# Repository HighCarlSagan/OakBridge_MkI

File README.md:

# OakBridge MkI

**A tactile PC dashboard — ESP32-S3, mechanical keys, IPS display, and a wooden enclosure.**

<p align="center">
  
  &nbsp;
  
</p>

---

## Why I Built This

I spend a lot of my day staring at terminals and dashboards. I wanted a small, tactile thing on the desk that could show me what my PC was doing without me having to alt-tab to find out — CPU temp during a long compile, what's playing on Spotify, calendar at a glance — and let me poke at it with real keys instead of yet another window.

The other half of the motivation is the stretch. OakBridge is the first project where I deliberately scoped a hardware → firmware → host-software stack end-to-end, all on parts I hadn't used in anger before: ESP32-S3, LVGL on a real display, FRAM for state, and a Python companion talking over MQTT. The point is to do the whole loop once, badly, and have a tangible thing on the desk afterwards.

The name is a nod to **oak wood** (the planned enclosure) and a small shout-out to **Oak Ridge National Laboratory**.

---

## Initial Requirements

The table below tracks the design intent against what will ship on **v1.1** (the DRC-fixed respin currently in fab, expected back end of May 2026). The first soldered board — **v1.0** — never powered up; see [Lessons Learned](#lessons-learned-the-0mm-via-incident) for the story. Until v1.1 lands, all power-up-dependent outcomes are honestly marked **TBD**.

| # | Requirement | Target | Outcome (v1.1) |
|---|---|---|---|
| 1 | MCU with WiFi + BLE + USB + enough headroom for LVGL | ESP32-S3 class | ✅ ESP32-S3-WROOM-1-N16R8 (16 MB flash, 8 MB PSRAM) |
| 2 | Display | ≥3" IPS, ≥320×240, SPI | ✅ Waveshare 3.5" IPS 320×480 (touch fanned out but unused in MkI) |
| 3 | Tactile input | Real mechanical keys with backlighting | ✅ 5× Cherry MX2A-E1NA + per-key backlight LEDs |
| 4 | Analog input | Rotary encoder with push | ✅ CUI ACZ11 (12 PPR, integrated switch) |
| 5 | Non-volatile state across reboots | FRAM, ≥1 Mbit | ✅ MB85RS4MTYPN (4 Mbit SPI FRAM) |
| 6 | Local storage for assets / logs | MicroSD socket | ✅ Hirose DM3BT push-push socket |
| 7 | Single-cable host connection | USB-C, power + serial | ✅ USB-C 2.0 + CDC-ACM virtual COM |
| 8 | Front-end protection | ESD + reverse-polarity + EMI filtering + fuse | ✅ USBLC6-2SC6 + SS14 + BLM18PG600 + 1.5A fuse |
| 9 | Power | USB 5V in, single 3.3V rail | ✅ TLV1117LV33 LDO (1A capacity, ~400 mA budget) |
| 10 | Board size | Comfortably hand-held footprint | ✅ 92 × 70 mm, 2-layer FR-4 |
| 11 | Manufacturability | Common SMD, hand-solderable | ✅ 0603 passives, QFN regulator, through-hole switches |
| 12 | Power-on bring-up | All rails verified | ⏳ TBD (waiting on v1.1) |
| 13 | Display, switches, encoder, FRAM verified | Hardware sign-off | ⏳ TBD |
| 14 | Firmware: LVGL, MQTT, OTA, mDNS | End-to-end on real board | ⏳ TBD |
| 15 | Wooden enclosure | Oak / walnut, parametric CAD | 🔄 In progress, on backburner |

---

## Specifications

| | |
|---|---|
| **MCU** | Espressif ESP32-S3-WROOM-1-N16R8 (Xtensa LX7 dual-core, 16 MB flash, 8 MB PSRAM) |
| **Display** | Waveshare 3.5" IPS, 320 × 480, SPI (touch fanned out, not wired up in firmware) |
| **Keys** | 5 × Cherry MX2A-E1NA, per-key blue backlight (Cree JE2835) |
| **Encoder** | CUI ACZ11BR1E-15KQA1-12C, 12 PPR with push |
| **NV storage** | MB85RS4MTYPN — 4 Mbit SPI FRAM |
| **Removable storage** | Hirose DM3BT-DSF-PEJS — push-push microSD socket |
| **Host interface** | USB-C 2.0, power + CDC-ACM serial |
| **Front-end protection** | 1.5 A fuse → SS14 reverse-polarity Schottky → BLM18PG600 ferrite → USBLC6-2SC6 ESD array |
| **Regulator** | TI TLV1117LV33 — 3.3 V LDO, 1 A capacity |
| **Power budget** | ~400 mA typical (estimate; bring-up will measure) |
| **PCB** | 92 × 70 mm, 2-layer FR-4, 1.6 mm, 1 oz copper, ENIG |
| **Aux switches** | BOOT + EN (ESP32 strap-pull), one extra tactile for firmware-defined use |
| **Mounting** | 4 × M3 holes (H1, H2, H6, H7) |

---

## Architecture

```
                ┌──────────────────────────────────────────────┐
                │                  USB-C (J1)                  │
                │      5 V power + USB 2.0 (D+ / D−)           │
                └──────────────────┬───────────────────────────┘
                                   │
                          ┌────────┴───────────────┐
                          │  Protection front-end  │
                          │  Fuse → SS14 → Ferrite │
                          │     → USBLC6 ESD       │
                          └────────┬───────────────┘
                                   │ 5 V
                          ┌────────┴────────┐
                          │   TLV1117LV33   │
                          │   5 V → 3.3 V   │
                          └────────┬────────┘
                                   │ 3.3 V (1 A)
                                   │
        ┌──────────────────────────┼──────────────────────────┐
        │                          │                          │
        ▼                          ▼                          ▼
┌────────────────┐       ┌─────────────────────┐    ┌───────────────────┐
│ ESP32-S3 N16R8 │       │  Waveshare 3.5" IPS │    │  MB85RS4MTYPN     │
│  WiFi + BLE    │◀─────▶│   320×480, SPI      │    │  4 Mbit SPI FRAM  │
│  USB-OTG       │       │   JST-GH 11-pin (J4)│    │   (state, config) │
└───┬────────┬───┘       └─────────────────────┘    └───────────────────┘
    │        │
    │        │            ┌──────────────────────┐
    │        ├──────────▶ │  microSD (DM3BT, J2) │
    │        │            │  logs, assets        │
    │        │            └──────────────────────┘
    │        │
    │        │            ┌──────────────────────┐
    │        └──────────▶ │  5 × Cherry MX2A     │
    │                     │  + 5 × backlight LEDs│
    │                     │  + CUI ACZ11 encoder │
    │                     │  + BOOT / EN / aux   │
    │                     └──────────────────────┘
    │
    ▼   (over WiFi)
┌──────────────────────────────┐
│  PC companion (Python)       │
│  CPU / GPU / RAM / media     │
│  → MQTT broker → OakBridge   │
└──────────────────────────────┘
```

---

## Why X over Y

A handful of decisions on this board that had real alternatives. Capturing them here so future-me remembers the trade.

**ESP32-S3 over ESP32 / RP2040.** The S3 has native USB (no CH340), enough SRAM + PSRAM to make LVGL pleasant, hardware vector ops, and WiFi + BLE on-chip. RP2040 would have been cheaper and easier to program but every wireless feature would have become a bolt-on. ESP32 (original) lacks native USB and is starting to feel its age for new designs.

**FRAM over EEPROM or flash-only.** State on this board (last screen, brightness, key bindings, MQTT credentials) gets written often enough that flash endurance is a real concern, and EEPROM is too small / too slow for anything beyond a few config bytes. FRAM is essentially RAM-fast, byte-writable, and rated for 10¹³ writes. Worth the few extra dollars.

**MicroSD + FRAM, not just FRAM.** FRAM holds *state*; SD holds *content* (UI assets, fonts, logs, image slideshow). Different access patterns, different lifetimes, different sizes. Keeping them separate keeps the firmware honest about what's small-and-precious vs. large-and-replaceable.

**TLV1117LV33 LDO over a buck.** Total budget is ~400 mA at 3.3 V from a 5 V source. Worst-case dissipation is (5 − 3.3) × 0.4 ≈ 0.7 W — comfortable for a SOT-223 with a copper pour. A buck would have been ~10–15% more efficient at the cost of switching noise on the analog encoder input, a bigger BOM, and an inductor. Not worth it at this current.

**2-layer board, not 4-layer.** Cheap to fab and the signal count is low enough to route on two layers without pain. The trade I made — and paid for — was that USB differential routing on a 2-layer stackup is fussier than I respected. See [Lessons Learned](#lessons-learned-the-0mm-via-incident). MkII may go 4-layer just for the routing comfort, not because anything on this board needs it electrically.

**Cherry MX2A over original MX.** The MX2A generation has smoother factory lubing and a quieter sound profile, and the footprint is drop-in compatible with classic MX. Same keycap ecosystem, slightly nicer feel.

**Touch fanned out but unused.** The Waveshare 3.5" comes with capacitive touch on the same FPC. I fanned the touch lines out to the connector but didn't wire them into firmware for MkI. Wanted to keep the firmware scope tractable; physical keys are the primary interaction. Touch becomes a v2 / MkII concern.

---

## Key Components

| Ref | Part | Function |
|---|---|---|
| U4 | ESP32-S3-WROOM-1-N16R8 | MCU + WiFi/BLE module |
| U3 | MB85RS4MTYPN-GS | 4 Mbit SPI FRAM |
| U2 | TLV1117LV33DCYR | 3.3 V / 1 A LDO |
| U1 | USBLC6-2SC6 | USB ESD protection array |
| J1 | GSB1C41110SSHR | USB Type-C 2.0 receptacle (Amphenol) |
| J2 | DM3BT-DSF-PEJS | Push-push microSD socket (Hirose) |
| J4 | BM11B-GHS-TBT | JST GH 11-pin (display FPC fanout) |
| MT1 | ACZ11BR1E-15KQA1-12C | CUI rotary encoder, 12 PPR + push |
| SW1–SW5 | Cherry MX2A-E1NA | Mechanical key switches |
| SW6 | TL1240YQ2JBLK | Auxiliary tactile (firmware-defined) |
| SW7, SW8 | SW_Push (THT) | ESP32 BOOT and EN |
| LED1–LED5 | Cree JE2835ARY-N | Per-key backlight (blue) |
| CR1 | SS14 | Schottky reverse-polarity protection |
| F1 | 1.5 A fuse (C1Q-series) | Input over-current |
| FL1 | BLM18PG600SN1D | EMI ferrite bead |
| R6, R7 | 5.1 kΩ | USB-C CC pull-downs (UFP role) |
| R30, R33–R35 | 0 Ω | Config straps (boot mode / interface selection) |

Full BOM: [`hardware/PC_Interface_Card/Exports/PC_Interface_Card.csv`](hardware/PC_Interface_Card/Exports/PC_Interface_Card.csv)
Netlist: [`hardware/PC_Interface_Card/Exports/PC_Interface_Card.net`](hardware/PC_Interface_Card/Exports/PC_Interface_Card.net)

---

## Connector Pinout

| Connector | Type | Purpose |
|---|---|---|
| J1 — USB-C | Amphenol GSB1C41110SSHR | 5 V power in + USB 2.0 data (UFP, CC pull-downs to GND via 5.1 kΩ) |
| J2 — microSD | Hirose DM3BT push-push | SPI to ESP32 (CD line wired) |
| J4 — Display | JST GH 11-pin | SPI MOSI/SCLK + DC/CS/RST + backlight enable + touch (unused) |
| MT1 — Encoder | Through-hole | A / B / SW pins (pull-ups on host side) |
| H1 / H2 / H6 / H7 | M3 mounting | Mechanical only |

Detailed pin-by-pin mapping will live in [`docs/pinout.md`](docs/pinout.md) once firmware development starts and pin assignments are locked.

---

## Firmware

**Status: not started.** Waiting for v1.1 boards to arrive before writing a single line. The plan below is the design intent, not a description of code that exists.

**Framework:** ESP-IDF v5.x
**Location:** `firmware/` (currently empty)

**Planned scope:**

- **Display:** LVGL on top of the Waveshare SPI driver, double-buffered, target 30+ FPS on simple screens.
- **Input:** software-debounced switches; quadrature decode for the encoder; long-press / multi-press detection.
- **Storage:** FRAM holds runtime config (brightness, current screen, key bindings, MQTT credentials). microSD holds fonts, icons, and any image assets.
- **Connectivity:** WiFi station mode, mDNS responder as `oakbridge.local`, MQTT client to a user-configured broker, embedded HTTP config server, OTA over WiFi.
- **PC link:** MQTT topics — `oakbridge/stats` (incoming PC metrics), `oakbridge/media` (now-playing), `oakbridge/commands` (outgoing key/encoder events). QoS 1.

Firmware build and flash instructions will land in [`docs/firmware_guide.md`](docs/firmware_guide.md) (planned).

### PC Companion

**Status: placeholder.** No code yet. The repo has a `companion/` directory reserved for it.

**Plan:** Python 3.8+ daemon that collects CPU / GPU / RAM / temperature stats via `psutil` and `pynvml`, reads media-player state via MPRIS on Linux, and publishes everything to MQTT for OakBridge to render. Linux first (my daily driver); Windows / macOS later if there's appetite.

---

## Setup & Bring-up

(Filled in after v1.1 boards arrive and bring-up completes.)

**Planned bring-up sequence:**

| Step | Action | Pass criterion |
|---|---|---|
| 1 | Power on via USB-C, no MCU loaded | 3.3 V rail measures 3.27–3.33 V, no thermal events |
| 2 | Probe ESP32 strap pins at reset | BOOT/EN behave correctly, no unexpected boot mode |
| 3 | Flash a minimal "hello UART" firmware | CDC-ACM enumerates, serial output visible |
| 4 | LED smoke test | Each of LED1–LED5 lights when driven |
| 5 | Switch + encoder smoke test | All 5 MX keys + encoder A/B/SW register |
| 6 | FRAM read/write test | Known-pattern write → power cycle → read back matches |
| 7 | microSD enumerate + read | FAT32 mount succeeds, files listable |
| 8 | Display init | Waveshare 3.5" shows colour bars |
| 9 | LVGL "hello" screen | First UI screen renders, encoder navigates |
| 10 | WiFi join + MQTT publish loop | `oakbridge/heartbeat` visible on broker |

Empty results table for backfill once boards arrive:

| Step | Result | Date | Notes |
|---|---|---|---|
| 1 | TBD | | |
| 2 | TBD | | |
| 3 | TBD | | |
| 4 | TBD | | |
| 5 | TBD | | |
| 6 | TBD | | |
| 7 | TBD | | |
| 8 | TBD | | |
| 9 | TBD | | |
| 10 | TBD | | |

---

## Hardware

**KiCad project:** [`hardware/PC_Interface_Card/`](hardware/PC_Interface_Card/) (KiCad 9.0)
**Schematic PDF:** [`hardware/docs/schematic.pdf`](hardware/docs/schematic.pdf)
**Gerbers:** [`hardware/PC_Interface_Card/Exports/Gerbers/`](hardware/PC_Interface_Card/Exports/Gerbers/) (v1.1, planned for end-of-May 2026)
**BOM:** [`hardware/PC_Interface_Card/Exports/PC_Interface_Card.csv`](hardware/PC_Interface_Card/Exports/PC_Interface_Card.csv)

### PCB Specifications

- **Size:** 92 × 70 mm
- **Layers:** 2-layer FR-4, 1.6 mm
- **Copper:** 1 oz (35 µm) outer
- **Finish:** ENIG
- **Min trace / clearance:** 0.15 mm / 0.15 mm (6 mil / 6 mil)
- **USB differential pair:** 0.35 mm width, 0.15 mm gap, target 90 Ω
- **Vias (v1.1):** 0.6 mm pad / 0.3 mm drill (signal); 0.8 mm / 0.4 mm (power)
- **Stitching:** ~50 GND vias

Design rule references:
- [`hardware/docs/pcb_design_rules.md`](hardware/docs/pcb_design_rules.md)
- [`hardware/docs/usb_routing_quick_ref.txt`](hardware/docs/usb_routing_quick_ref.txt)
- [`hardware/docs/kicad_design_rules.json`](hardware/docs/kicad_design_rules.json)

### Enclosure

A wooden enclosure (oak) is planned. CAD work is in progress and on the backburner while the v1.1 PCB respin and firmware bring-up take priority. Parametric files will land in [`enclosure/`](enclosure/) once the design is ready.

---

## Lessons Learned: the 0mm-via incident

The v1.0 board does not work. It does not even power up — I haven't tried, because the failure is structural, not electrical.

**What happened.** When I set up the PCB design rules in KiCad, I left the **via drill diameter at 0 mm** in one of the via classes. KiCad's DRC would have caught this immediately. I skipped DRC verification before exporting Gerbers, because the layout was "obviously fine" — I had reviewed it visually and the renders looked clean. The fab took the files as-is, produced the board with pads where vias should have been, and shipped it. I soldered the whole thing before realising every via on the affected net class was just a copper dot with no hole through the board.

**What I'm doing about it.**

1. **v1.1 is in fab.** Same design, drill diameters corrected, going turnkey this time so I get a populated board back. Expected end of May 2026.
2. **DRC is no longer optional.** From now on, "DRC pass" is a step in my export checklist that has to be ticked before Gerbers leave my machine. I've added a one-line note to my KiCad project template.
3. **I review fab DFM reports.** Most fabs *do* run DFM checks and flag missing drills. This one didn't, or did and I missed the email. Either way, the responsibility is on me to verify, not on them to warn.

**Why this is in the README and not buried.** The whole point of these write-ups is to be honest about how the work actually went. The board is broken because I made an avoidable mistake. Documenting it costs me nothing and saves the next person (probably future-me, on a different project) from doing the same thing. It also makes everything *else* in this README more credible.

More detail in [`docs/lessons-learned.md`](docs/lessons-learned.md).

---

## Repository Structure

```
OakBridge_MkI/
├── hardware/
│   ├── PC_Interface_Card/         # KiCad 9.0 project
│   │   ├── PC_Interface_Card.kicad_pro
│   │   ├── PC_Interface_Card.kicad_sch
│   │   ├── PC_Interface_Card.kicad_pcb
│   │   ├── Libraries/             # Custom symbols + footprints
│   │   └── Exports/
│   │       ├── Gerbers/
│   │       ├── PC_Interface_Card.csv     # BOM
│   │       ├── PC_Interface_Card.net     # Netlist
│   │       ├── PC_Interface_Card_Top.jpg
│   │       └── PC_Interface_Card_Bot.jpg
│   └── docs/
│       ├── schematic.pdf
│       ├── pcb_design_rules.md
│       ├── usb_routing_quick_ref.txt
│       └── kicad_design_rules.json
├── firmware/                      # ESP-IDF project (planned)
├── companion/                     # Python PC companion (placeholder)
├── enclosure/                     # Oak enclosure CAD (in progress)
├── docs/
│   ├── lessons-learned.md
│   ├── firmware_guide.md          # planned
│   ├── pinout.md                  # planned
│   └── images/
├── LICENSE
└── README.md
```

---

## When to Use This / When NOT to Use This

**Use this if you want to:**
- Build a tactile, mechanical-key dashboard for your own PC, on your own desk, with your own UI.
- Learn ESP32-S3, LVGL, FRAM, and MQTT together on one small board.
- Fork the design as a starting point for any "small wireless gadget with a screen and a few buttons" project.

**Don't use this if you want to:**
- A polished, validated, production-ready product. This is a personal learning project. v1.0 didn't power up. v1.1 is in fab.
- A keyboard. 5 keys is not a keyboard. If you want a macropad, the Cherry MX footprints are reusable but you'd be better off with a project actually scoped as a macropad.
- A low-latency input device for gaming. USB-CDC + MQTT has latencies that are fine for "skip track" and bad for "fire weapon".

---

## Roadmap

### v1.0 — soldered, dud (May 2026)
PCBs fabricated and hand-soldered. Discovered the 0mm-via DRC miss after assembly. Never powered up. Kept on the desk as a reminder.

### v1.1 — DRC-fixed respin (end of May 2026, in fab)
- ✅ Drill diameters corrected, DRC clean, Gerbers re-exported
- ⏳ Turnkey assembly with the fab — boards arrive populated
- ⏳ Power-on bring-up (table above)
- ⏳ Firmware v0.1 — display init, switches, encoder, FRAM read/write
- ⏳ Firmware v0.2 — WiFi + MQTT + first PC-companion round-trip
- 🔄 Enclosure CAD (oak) — in progress, no committed date

### MkII — possibilities (much later, ~2027)

Not committed. Listing what I'd consider if I redesigned from scratch:

- 4-layer stackup for cleaner USB / display routing
- Capacitive touch wired into firmware (FPC fanout already exists)
- USB-C PD negotiation for higher current headroom
- Side-mount encoder for a flatter front face
- Independent RGB backlight per key (currently single-channel blue)

---

## License

**Hardware:** [CERN Open Hardware Licence Version 2 — Permissive (CERN-OHL-P-2.0)](LICENSE)
**Firmware** (when it exists): MIT
**Documentation:** CC-BY-4.0

You're free to use, modify, fabricate, and distribute the hardware design with attribution. No reciprocity required.

---

## Related Projects

- **[PC_and_Light_Controller](https://github.com/HighCarlSagan/PC_and_Light_Controller)** — sibling desk-control project. PC_and_Light_Controller handles physical switching of mains-powered desk devices; OakBridge handles the on-desk informational layer. Different problems, same desk.
- **[Dual_Power_Supply](https://github.com/HighCarlSagan/Dual_Power_Supply)** — my benchtop linear supply. The supply that probed v1.0 and confirmed the bad news.
- **[Carls_Homelab_Public](https://github.com/HighCarlSagan/Carls_Homelab_Public)** — where the MQTT broker will eventually live.

---

## Author

**Mayank S (HighCarlSagan)** — [GitHub @HighCarlSagan](https://github.com/HighCarlSagan) · [highcarlsagan.dev](https://highcarlsagan.dev)

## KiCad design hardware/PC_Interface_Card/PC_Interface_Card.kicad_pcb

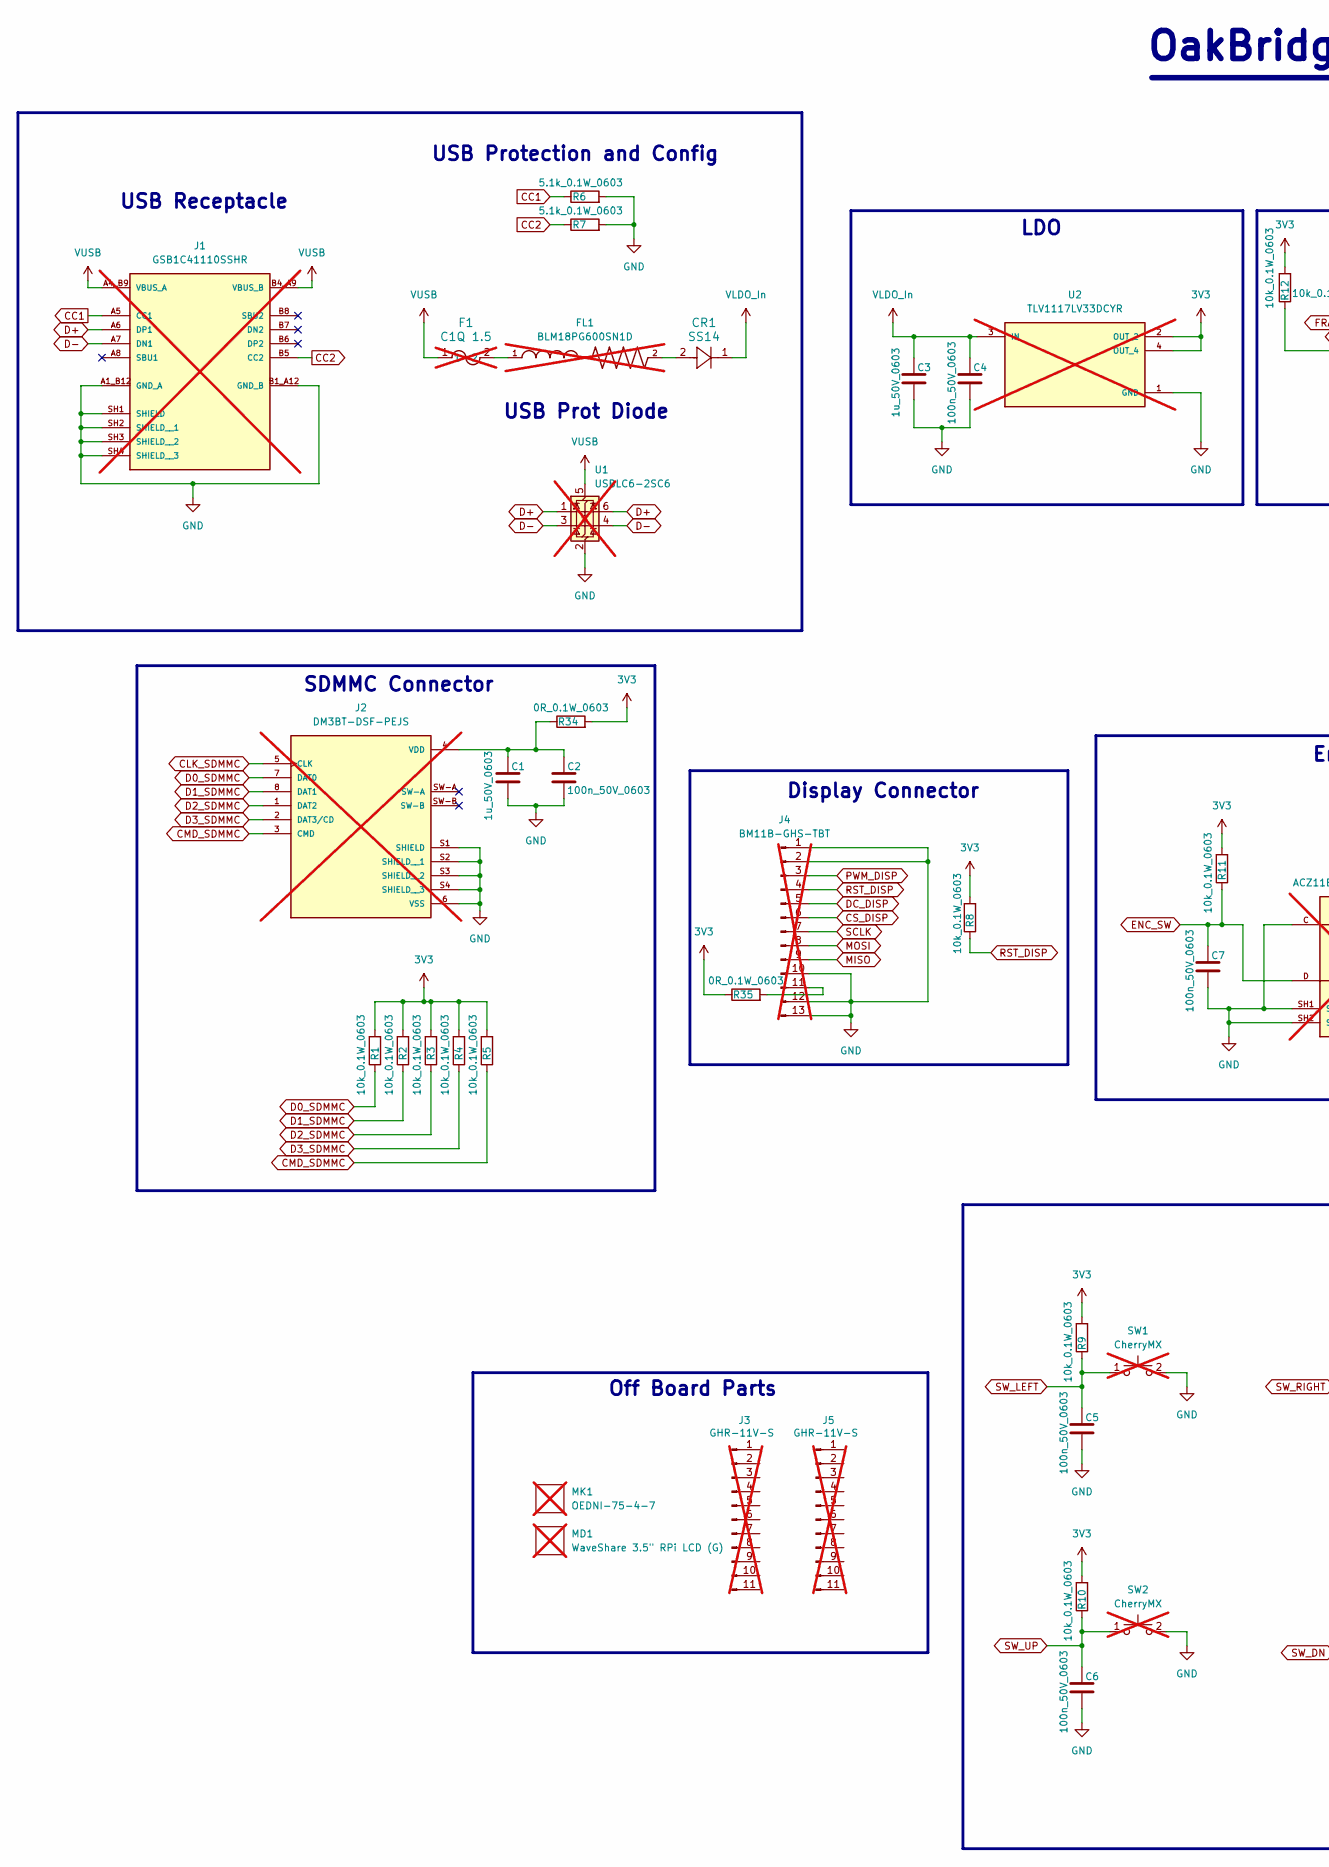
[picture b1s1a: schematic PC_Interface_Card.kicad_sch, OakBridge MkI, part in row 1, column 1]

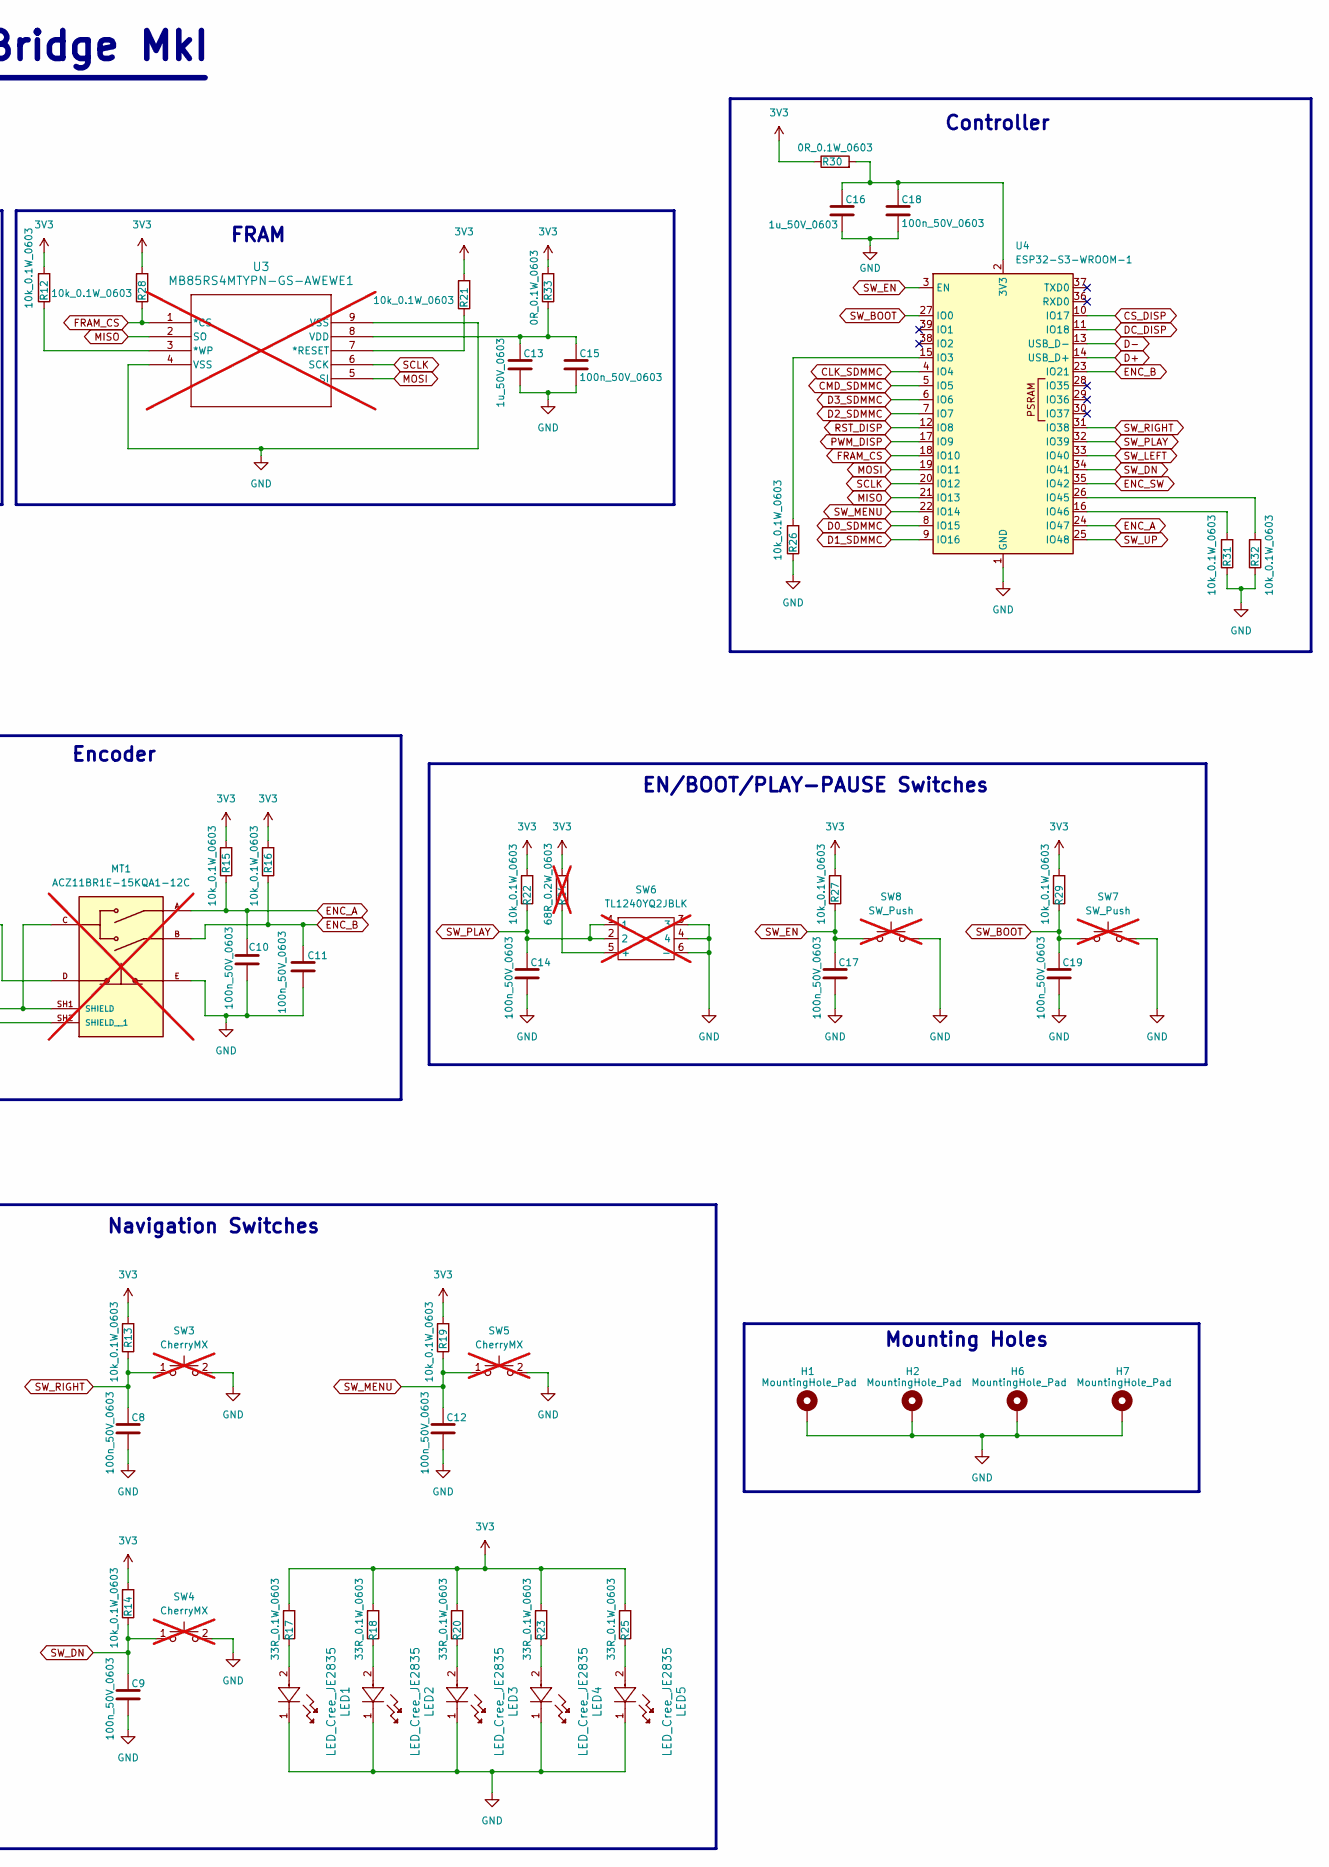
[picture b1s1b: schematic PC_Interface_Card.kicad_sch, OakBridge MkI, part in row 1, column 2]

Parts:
C1, C3, C13, C16: 1u_50V_0603; C_0603_1608Metric; Manufacturer Part Number C0603C105K4RACTU; LCSC C15849
C2, C4, C5, C6, C7, C8, C9, C10, C11, C12, C14, C15, C17, C18, C19: 100n_50V_0603; C_0603_1608Metric; Manufacturer Part Number CC0603KRX7R7BB104; LCSC C14663
CR1: SS14; D_SMA; Manufacturer Part Number SS14; LCSC C2480
F1: C1Q 1.5; C1_BEL-M; Manufacturer Part Number C1Q 1.5; not fitted
FL1: BLM18PG600SN1D; BEAD_BLM18PG_C1608X95N; Manufacturer Part Number BLM18PG600SN1D; not fitted
H1, H2, H6, H7: MountingHole_Pad; MountingHole_2.2mm_M2_Pad_Via
J1: GSB1C41110SSHR; AMPHENOL_GSB1C41110SSHR; Manufacturer Part Number GSB1C41110SSHR; not fitted
J2: DM3BT-DSF-PEJS; HRS_DM3BT-DSF-PEJS; Manufacturer Part Number DM3BT-DSF-PEJS; not fitted
J3, J5: GHR-11V-S; Manufacturer Part Number GHR-11V-S; not fitted
J4: BM11B-GHS-TBT; CONN11_BM11B-GHS-TBTLFSNN_JST; Manufacturer Part Number BM11B-GHS-TBT; not fitted
LED1, LED2, LED3, LED4, LED5: LED_Cree_JE2835; LED_JE2835_CRW-M; Manufacturer Part Number JE2835ARY-N-0002A0000-N0000001
MD1: WaveShare 3.5" RPi LCD (G); Manufacturer Part Number 30897; not fitted
MK1: OEDNI-75-4-7; Manufacturer Part Number OEDNI-75-4-7; not fitted
MT1: ACZ11BR1E-15KQA1-12C; XDCR_ACZ11BR1E-15KQA1-12C; Manufacturer Part Number ACZ11BR1E-15KQA1-12C; not fitted
R1, R2, R3, R4, R5, R8, R9, R10, R11, R12, R13, R14, R15, R16, R19, R21, R22, R26, R27, R28, R29, R31, R32: 10k_0.1W_0603; R_0603_1608Metric; Manufacturer Part Number ERJ-PB3B1002V; LCSC C25804
R6, R7: 5.1k_0.1W_0603; R_0603_1608Metric; Manufacturer Part Number ERJ-PB3B5101V; LCSC C23186
R17, R18, R20, R23, R25: 33R_0.1W_0603; R_0603_1608Metric; Manufacturer Part Number CRGH0603J33R; LCSC C23140
R24: 68R_0.2W_0603; R_0603_1608Metric; Manufacturer Part Number RC0603FR-7W68RL; not fitted
R30, R33, R34, R35: 0R_0.1W_0603; R_0603_1608Metric; LCSC C21189
SW1, SW2, SW3, SW4, SW5: CherryMX; CherryMX_1.00u_PCB; Manufacturer Part Number MX2A-E1NA; not fitted
SW6: TL1240YQ2JBLK; TL1240YQ; Manufacturer Part Number TL1240YQ2JBLK; not fitted
SW7, SW8: SW_Push; SW_PUSH_6mm; not fitted
U1: USBLC6-2SC6; SOT-23-6; Manufacturer Part Number USBLC6-2SC6; not fitted
U2: TLV1117LV33DCYR; VREG_TLV1117LV33DCYR; Manufacturer Part Number TLV1117LV33DCYR; not fitted
U3: MB85RS4MTYPN-GS-AWEWE1; DFN8_FUJ-M; Manufacturer Part Number MB85RS4MTYPF-G-BCE1; not fitted
U4: ESP32-S3-WROOM-1; ESP32-S3-WROOM-1U; Manufacturer Part Number ESP32-S3-WROOM-1-N16R8; LCSC C2913202

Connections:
3V3: R1.2, R2.2, R3.2, R4.2, R5.2, R8.2, R9.2, R10.2, R11.2, R12.2, R13.2, R14.2, R15.2, R16.2, R17.2, R18.2, R19.2, R20.2, R21.2, R22.2, R23.2, R24.2, R25.2, R27.2, R28.2, R29.2, R30.1, R33.2, R34.2, R35.1, U2.2 (OUT_2), U2.4 (OUT_4)
CC1: J1.A5 (CC1), R6.1
CC2: J1.B5 (CC2), R7.1
CLK_SDMMC: J2.5 (CLK), U4.4 (IO4)
CMD_SDMMC: J2.3 (CMD), R5.1, U4.5 (IO5)
CS_DISP: J4.6, U4.10 (IO17)
D0_SDMMC: J2.7 (DAT0), R1.1, U4.8 (IO15)
D1_SDMMC: J2.8 (DAT1), R2.1, U4.9 (IO16)
D2_SDMMC: J2.1 (DAT2), R3.1, U4.7 (IO7)
D3_SDMMC: J2.2 (DAT3/CD), R4.1, U4.6 (IO6)
D+: J1.A6 (DP1), U1.1 (I/O1), U1.6 (I/O1), U4.14 (USB_D+)
D-: J1.A7 (DN1), U1.3 (I/O2), U1.4 (I/O2), U4.13 (USB_D-)
DC_DISP: J4.5, U4.11 (IO18)
ENC_A: C10.1, MT1.A, R15.1, U4.24 (IO47)
ENC_B: C11.1, MT1.B, R16.1, U4.23 (IO21)
ENC_SW: C7.1, MT1.D, R11.1, U4.35 (IO42)
FRAM_CS: R28.1, U3.1 (*CS), U4.18 (IO10)
GND: C1.2, C2.2, C3.2, C4.2, C5.2, C6.2, C7.2, C8.2, C9.2, C10.2, C11.2, C12.2, C13.2, C14.2, C15.2, C16.2, C17.2, C18.2, C19.2, H1.1 (1_1), H2.1 (1_1), H6.1 (1_1), H7.1 (1_1), J1.A1_B12 (GND_A), J1.B1_A12 (GND_B), J1.SH1 (SHIELD), J1.SH2 (SHIELD__1), J1.SH3 (SHIELD__2), J1.SH4 (SHIELD__3), J2.6 (VSS), J2.S1 (SHIELD), J2.S2 (SHIELD__1), J2.S3 (SHIELD__2), J2.S4 (SHIELD__3), J4.1, J4.2, J4.10, J4.12, J4.13, LED1.1, LED2.1, LED3.1, LED4.1, LED5.1, MT1.C, MT1.E, MT1.SH1 (SHIELD), MT1.SH2 (SHIELD__1), R6.2, R7.2, R26.1, R31.1, R32.1, SW1.2, SW2.2, SW3.2, SW4.2, SW5.2, SW6.3, SW6.4, SW6.6 (-), SW7.2, SW8.2, U1.2 (GND), U2.1 (GND), U3.4 (VSS), U3.9 (VSS), U4.1 (GND), U4.40 (GND), U4.41 (GND)
MISO: J4.9, U3.2 (SO), U4.21 (IO13)
MOSI: J4.8, U3.5 (SI), U4.19 (IO11)
unnamed: CR1.2, FL1.2
unnamed: F1.2, FL1.1
unnamed: C1.1, C2.1, J2.4 (VDD), R34.1
unnamed: J4.11, R35.2
unnamed: LED1.2, R17.1
unnamed: LED2.2, R18.1
unnamed: LED3.2, R20.1
unnamed: LED4.2, R23.1
unnamed: LED5.2, R25.1
unnamed: R24.1, SW6.5 (+)
unnamed: R21.1, U3.7 (*RESET)
unnamed: R12.1, U3.3 (*WP)
unnamed: C13.1, C15.1, R33.1, U3.8 (VDD)
unnamed: C16.1, C18.1, R30.2, U4.2 (3V3)
unnamed: R26.2, U4.15 (IO3)
unnamed: R32.2, U4.26 (IO45)
unnamed: R31.2, U4.16 (IO46)
PWM_DISP: J4.3, U4.17 (IO9)
RST_DISP: J4.4, R8.1, U4.12 (IO8)
SCLK: J4.7, U3.6 (SCK), U4.20 (IO12)
SW_BOOT: C19.1, R29.1, SW7.1, U4.27 (IO0)
SW_DN: C9.1, R14.1, SW4.1, U4.34 (IO41)
SW_EN: C17.1, R27.1, SW8.1, U4.3 (EN)
SW_LEFT: C5.1, R9.1, SW1.1, U4.33 (IO40)
SW_MENU: C12.1, R19.1, SW5.1, U4.22 (IO14)
SW_PLAY: C14.1, R22.1, SW6.1, SW6.2, U4.32 (IO39)
SW_RIGHT: C8.1, R13.1, SW3.1, U4.31 (IO38)
SW_UP: C6.1, R10.1, SW2.1, U4.25 (IO48)
VLDO_In: C3.1, C4.1, CR1.1, U2.3 (IN)
VUSB: F1.1, J1.A4_B9 (VBUS_A), J1.B4_A9 (VBUS_B), U1.5 (VBUS)

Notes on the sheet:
USB Protection and Config
USB Receptacle
Encoder
USB Prot Diode
Mounting Holes
LDO
OakBridge MkI
Navigation Switches
Display Connector
SDMMC Connector
Controller
Off Board Parts
EN/BOOT/PLAY-PAUSE Switches
FRAM

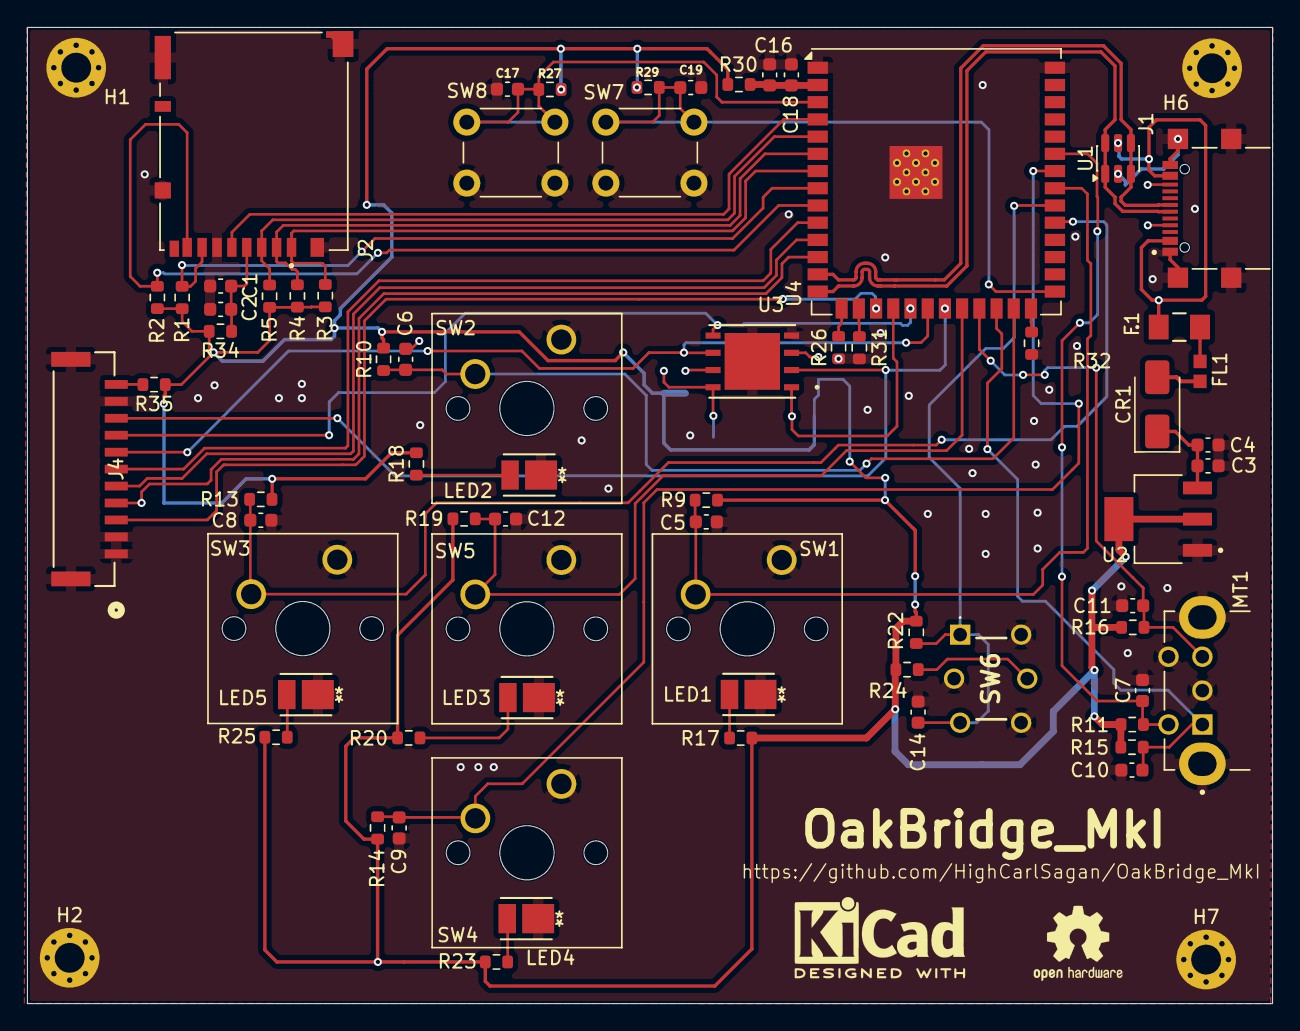
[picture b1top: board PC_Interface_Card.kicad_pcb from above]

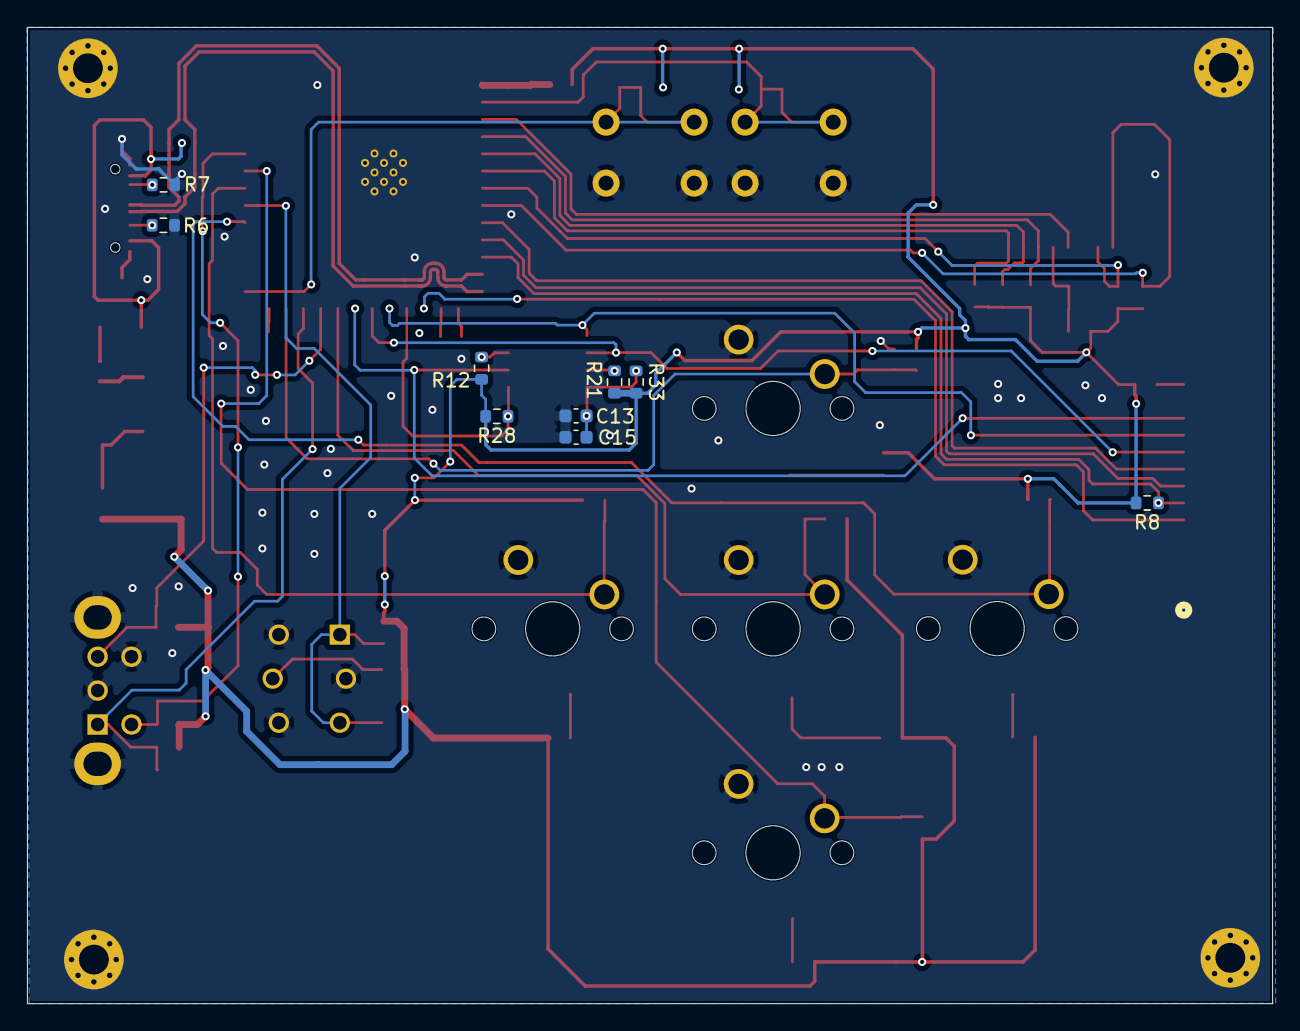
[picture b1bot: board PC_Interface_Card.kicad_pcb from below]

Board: 2 copper layers, 91.9 x 72.0 mm, 82 parts (9 on the bottom side), 50 nets.

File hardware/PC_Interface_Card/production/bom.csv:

Designator,Footprint,Quantity,Value,LCSC Part #
"C1, C13, C16, C3",0603,4,1u_50V_0603,C15849
"C10, C11, C12, C14, C15, C17, C18, C19, C2, C4, C5, C6, C7, C8, C9",0603,15,100n_50V_0603,C14663
CR1,D_SMA,1,SS14,C2480
F1,C1_BEL-M,1,C1Q 1.5,
FL1,BEAD_BLM18PG_C1608X95N,1,BLM18PG600SN1D,
J1,AMPHENOL_GSB1C41110SSHR,1,GSB1C41110SSHR,
J2,HRS_DM3BT-DSF-PEJS,1,DM3BT-DSF-PEJS,
J4,CONN11_BM11B-GHS-TBTLFSNN_JST,1,BM11B-GHS-TBT,
"LED1, LED2, LED3, LED4, LED5",LED_JE2835_CRW-M,5,LED_Cree_JE2835,
MT1,XDCR_ACZ11BR1E-15KQA1-12C,1,ACZ11BR1E-15KQA1-12C,
"R1, R10, R11, R12, R13, R14, R15, R16, R19, R2, R21, R22, R26, R27, R28, R29, R3, R31, R32, R4, R5, R8, R9",0603,23,10k_0.1W_0603,C25804
"R17, R18, R20, R23, R25",0603,5,33R_0.1W_0603,C23140
R24,0603,1,68R_0.2W_0603,
"R30, R33, R34, R35",0603,4,0R_0.1W_0603,C21189
"R6, R7",0603,2,5.1k_0.1W_0603,C23186
"SW1, SW2, SW3, SW4, SW5",CherryMX_1.00u_PCB,5,CherryMX,
SW6,TL1240YQ,1,TL1240YQ2JBLK,
"SW7, SW8",SW_PUSH_6mm,2,SW_Push,
U1,SOT-23-6,1,USBLC6-2SC6,
U2,VREG_TLV1117LV33DCYR,1,TLV1117LV33DCYR,
U3,DFN8_FUJ-M,1,MB85RS4MTYPN-GS-AWEWE1,
U4,ESP32-S3-WROOM-1U,1,ESP32-S3-WROOM-1,C2913202

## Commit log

2026-01-11 Updated final schematic, BoM and footprint assignment, imported schema to PCB
2026-01-11 footprint and 3d model fixes, footprint mismatch persists for B3W-9000 still. Need a fix.
2026-01-13 Schematic changes
2026-01-13 schematic pdf
2026-01-15 Footprints added with BoM update and all 3d models added.
2026-01-15 More BoM fixes and 3D models, off board parts added.
2026-01-15 Changed encoder to a right angle one
2026-01-15 footprint fixes
2026-01-16 Added via and trace rules
2026-01-24 Start of day work - 24/01
2026-01-24 Saving data for the day - added dxf for display and component placement
2026-01-24 Alignment of moounting holes and final layout
2026-01-25 More layout work - Display SPI and differential pair DRC pending
2026-01-25 More alyout work, added DRC Error output for 26012026
2026-02-01 layout changes
2026-02-06 Saving work with smaller board changes
2026-02-06 Some DRC errors remain - clarifications on Monday then fab
2026-02-15 Manufacturing Readiness
2026-02-15 Added images
2026-04-20 Fixes on the layout for refab due to my copyrighted SMD vias
2026-04-21 MkII ready to fab but SMD via error still coming on JLCPCB gerber viewer - need to figure out why and close
2026-05-11 docs: rewrite README, add lessons-learned, swap to CERN-OHL-P-2.0

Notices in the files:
README.md:
License: CERN-OHL-P-2.0
